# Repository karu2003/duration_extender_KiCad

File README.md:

# Duration Extender for Laser Pulse Receiver

## Description

This project is intended for testing the circuit from the repository:  
https://github.com/karu2003/small_projects/tree/master/laser_sound_card

The device increases the duration of the input signal coming from the laser pulse receiver (pulse duration — 3 ns).  
This is necessary for correct processing of the signal by the Raspberry Pi Pico microcontroller using the PIO block.  
Thanks to this, even very short pulses from the laser become long enough to be reliably processed in digital logic.

## Schematic

## Links

- [KiCad](https://github.com/karu2003/small_projects/tree/master/laser_sound_card)

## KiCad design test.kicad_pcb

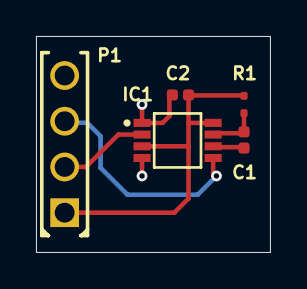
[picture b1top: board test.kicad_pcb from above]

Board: 2 copper layers, 13.0 x 12.0 mm, 5 parts (0 on the bottom side), 6 nets.

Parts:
C1: 22pF; CAPC1005X55N
C2: 0.1µF; CAPC1005X55N
IC1: 74LVC1G123DP,125; TSSOP8
P1: M20-9990446; HDR1X4
R1: 1k; RESC1005X04L

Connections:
GND: C2.1, IC1.1, IC1.4, P1.4
NetC1_1: C1.1, IC1.6
NetC1_2: C1.2, IC1.7, R1.1
NetIC1_2: IC1.2, P1.2
NetIC1_5: IC1.5, P1.3
VCC: C2.2, IC1.3, IC1.8, P1.1, R1.2

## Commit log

2025-08-16 add KiCad
